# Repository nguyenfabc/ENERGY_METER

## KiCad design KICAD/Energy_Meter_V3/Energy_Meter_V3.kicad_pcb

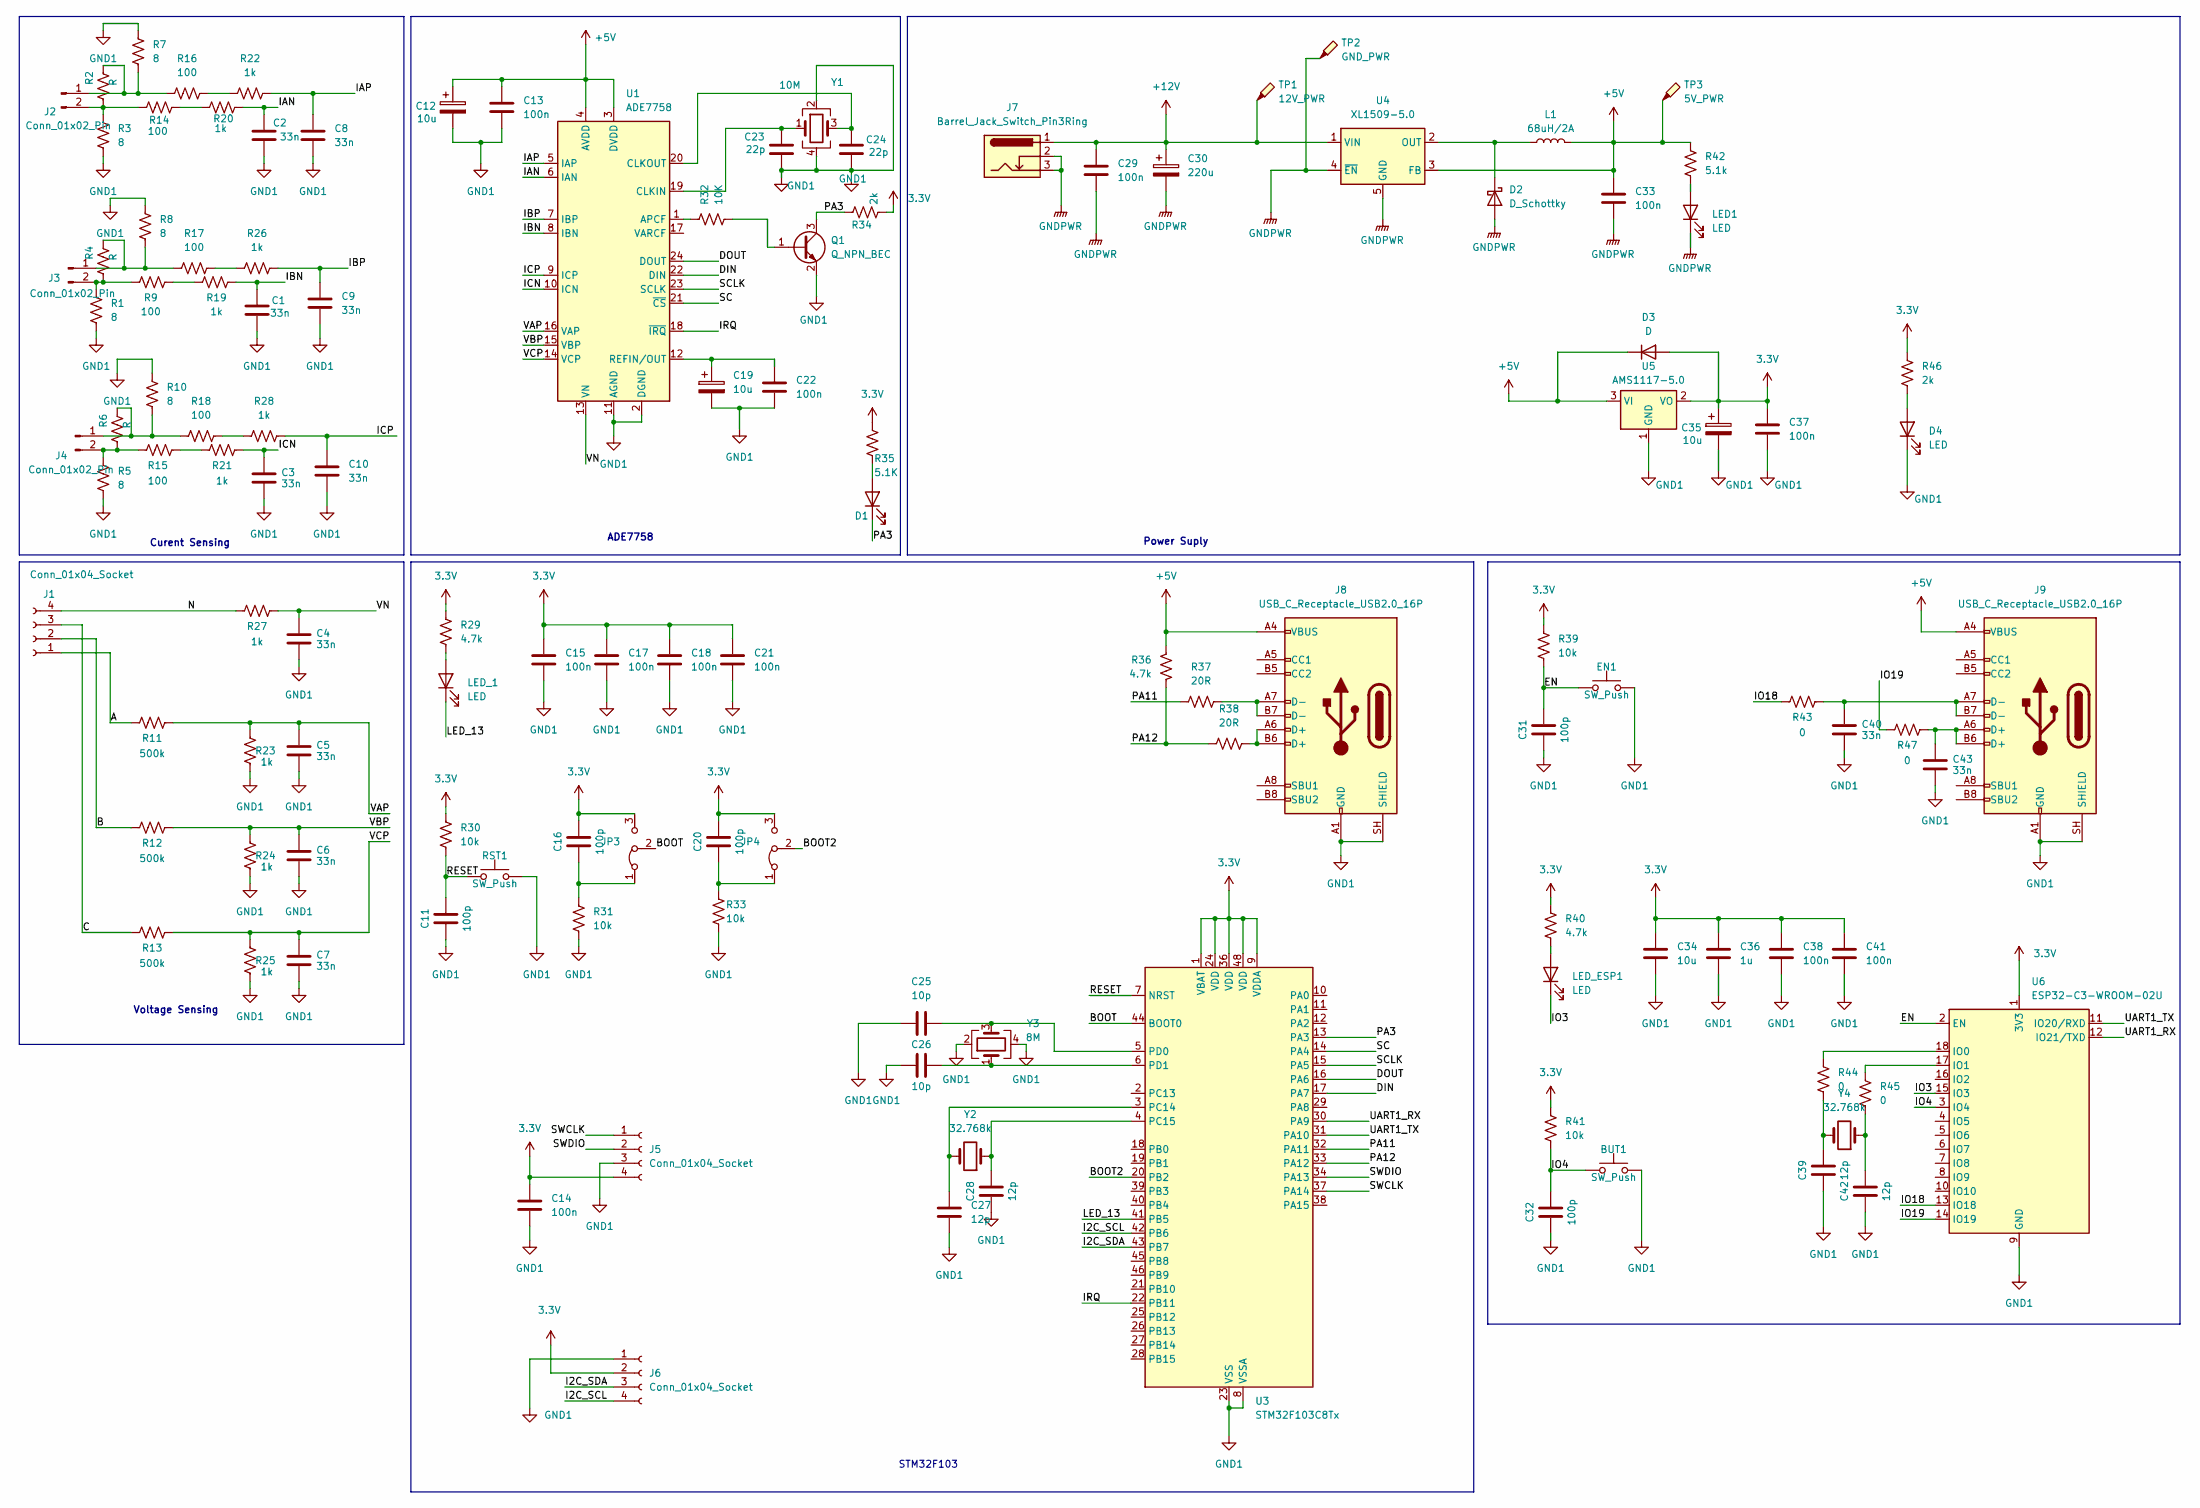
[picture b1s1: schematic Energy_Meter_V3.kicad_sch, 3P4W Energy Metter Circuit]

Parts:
BUT1: SW_Push; SW_SPST_CK_RS282G05A3
C1, C2, C3, C4, C5, C6, C7, C8, C9, C10, C40, C43: 33n; C_0603_1608Metric_Pad1.08x0.95mm_HandSolder
C11, C16, C20, C31, C32: 100p; C_0603_1608Metric_Pad1.08x0.95mm_HandSolder
C12, C19: 10u; CP_EIA-3216-10_Kemet-I_HandSolder
C13, C14, C15, C17, C18, C21, C22, C29, C33, C37, C38, C41: 100n; C_0603_1608Metric_Pad1.08x0.95mm_HandSolder
C23, C24: 22p; C_0603_1608Metric_Pad1.08x0.95mm_HandSolder
C25, C26: 10p; C_0603_1608Metric_Pad1.08x0.95mm_HandSolder
C27, C28, C39, C42: 12p; C_0603_1608Metric_Pad1.08x0.95mm_HandSolder
C30: 220u; CP_Elec_6.3x7.7
C34: 10u; C_0603_1608Metric_Pad1.08x0.95mm_HandSolder
C35: 10u; CP_Elec_4x5.4
C36: 1u; C_0603_1608Metric_Pad1.08x0.95mm_HandSolder
D1, D4: LED; LED_0805_2012Metric_Pad1.15x1.40mm_HandSolder
D2: D_Schottky; D_SMA_Handsoldering
D3: D; D_SMA_Handsoldering
EN1: SW_Push; SW_SPST_CK_RS282G05A3
J1: Conn_01x04_Socket; TerminalBlock_Phoenix_MKDS-1,5-4_1x04_P5.00mm_Horizontal
J2, J3, J4: Conn_01x02_Pin; TerminalBlock_Phoenix_MKDS-1,5-2_1x02_P5.00mm_Horizontal
J5: Conn_01x04_Socket; PinHeader_1x04_P2.54mm_Vertical
J6: Conn_01x04_Socket; PinSocket_1x04_P2.54mm_Vertical
J7: Barrel_Jack_Switch_Pin3Ring; BarrelJack_Kycon_KLDX-0202-xC_Horizontal
J8, J9: USB_C_Receptacle_USB2.0_16P; USB_C_Receptacle_Palconn_UTC16-G
JP3, JP4: Jumper_3_Bridged12; PinHeader_1x03_P2.54mm_Vertical
L1: 68uH/2A; L_Bourns_SRP7028A_7.3x6.6mm
LED1: LED; LED_0805_2012Metric_Pad1.15x1.40mm_HandSolder
LED_1: LED; LED_0805_2012Metric_Pad1.15x1.40mm_HandSolder
LED_ESP1: LED; LED_0805_2012Metric_Pad1.15x1.40mm_HandSolder
Q1: Q_NPN_BEC; SOT-23
R1, R3, R5, R7, R8, R10: 8; R_0603_1608Metric_Pad0.98x0.95mm_HandSolder
R2, R4, R6: R; R_0603_1608Metric_Pad0.98x0.95mm_HandSolder
R9, R14, R15, R16, R17, R18: 100; R_0603_1608Metric_Pad0.98x0.95mm_HandSolder
R11, R12, R13: 500k; R_0603_1608Metric_Pad0.98x0.95mm_HandSolder
R19, R20, R21, R22, R23, R24, R25, R26, R27, R28: 1k; R_0603_1608Metric_Pad0.98x0.95mm_HandSolder
R29, R36, R40: 4.7k; R_0603_1608Metric_Pad0.98x0.95mm_HandSolder
R30, R31, R33, R39, R41: 10k; R_0603_1608Metric_Pad0.98x0.95mm_HandSolder
R32: 10K; R_0603_1608Metric_Pad0.98x0.95mm_HandSolder
R34, R46: 2k; R_0603_1608Metric_Pad0.98x0.95mm_HandSolder
R35: 5.1K; R_0603_1608Metric_Pad0.98x0.95mm_HandSolder
R37, R38: 20R; R_0603_1608Metric_Pad0.98x0.95mm_HandSolder
R42: 5.1k; R_0603_1608Metric_Pad0.98x0.95mm_HandSolder
R43, R44, R45, R47: 0; R_0603_1608Metric_Pad0.98x0.95mm_HandSolder
RST1: SW_Push; SW_SPST_CK_RS282G05A3
TP1: 12V_PWR; TestPoint_Loop_D1.80mm_Drill1.0mm_Beaded
TP2: GND_PWR; TestPoint_Loop_D1.80mm_Drill1.0mm_Beaded
TP3: 5V_PWR; TestPoint_Loop_D1.80mm_Drill1.0mm_Beaded
U1: ADE7758; SOIC-24W_7.5x15.4mm_P1.27mm
U3: STM32F103C8Tx; LQFP-48_7x7mm_P0.5mm
U4: XL1509-5.0; SOIC-8_3.9x4.9mm_P1.27mm
U5: AMS1117-5.0; SOT-223-3_TabPin2
U6: ESP32-C3-WROOM-02U
Y1: 10M; Crystal_SMD_5032-4Pin_5.0x3.2mm
Y2, Y4: 32.768k; Crystal_SMD_3215-2Pin_3.2x1.5mm
Y3: 8M; Crystal_SMD_5032-4Pin_5.0x3.2mm

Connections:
3.3V: C14.2, C15.2, C16.2, C17.2, C18.2, C20.2, C21.2, C34.2, C35.1, C36.2, C37.1, C38.2, C41.2, D3.2 (A), J5.4, J6.2, JP3.3 (B), JP4.3 (B), R29.1, R30.1, R34.1, R35.2, R39.1, R40.1, R41.1, R46.2, U3.1 (VBAT), U3.9 (VDDA), U3.24 (VDD), U3.36 (VDD), U3.48 (VDD), U5.2 (VO), U6.1 (3V3)
+5V: C12.1, C13.1, C33.2, D3.1 (K), J8.A4 (VBUS), J8.A9 (VBUS), J8.B4 (VBUS), J8.B9 (VBUS), J9.A4 (VBUS), J9.A9 (VBUS), J9.B4 (VBUS), J9.B9 (VBUS), L1.2, R36.1, R42.1, TP3.1 (1_1), U1.3 (DVDD), U1.4 (AVDD), U4.3 (FB), U5.3 (VI)
+12V: C29.2, C30.1, J7.1, TP1.1 (1_1), U4.1 (VIN)
/A: J1.1, R11.1
/B: J1.2, R12.1
/BOOT: JP3.2 (C), U3.44 (BOOT0)
/BOOT2: JP4.2 (C), U3.20 (PB2)
/C: J1.3, R13.1
/DIN: U1.22 (DIN), U3.17 (PA7)
/DOUT: U1.24 (DOUT), U3.16 (PA6)
/EN: C31.2, EN1.1, R39.2, U6.2 (EN)
/I2C_SCL: J6.4, U3.42 (PB6)
/I2C_SDA: J6.3, U3.43 (PB7)
/IAN: C2.1, R20.2, U1.6 (IAN)
/IAP: C8.1, R22.2, U1.5 (IAP)
/IBN: C1.1, R19.2, U1.8 (IBN)
/IBP: C9.1, R26.2, U1.7 (IBP)
/ICN: C3.1, R21.2, U1.10 (ICN)
/ICP: C10.1, R28.2, U1.9 (ICP)
/IO3: LED_ESP1.1 (K), U6.15 (IO3)
/IO4: BUT1.1, C32.2, R41.2, U6.3 (IO4)
/IO18: R43.1, U6.13 (IO18)
/IO19: R47.1, U6.14 (IO19)
/IRQ: U1.18 (~IRQ), U3.22 (PB11)
/LED_13: LED_1.1 (K), U3.41 (PB5)
/N: J1.4, R27.1
/PA3: D1.1 (K), Q1.3 (C), R34.2, U3.13 (PA3)
/PA11: R37.1, U3.32 (PA11)
/PA12: R36.2, R38.1, U3.33 (PA12)
/RESET: C11.2, R30.2, RST1.1, U3.7 (NRST)
/SC: U1.21 (~CS), U3.14 (PA4)
/SCLK: U1.23 (SCLK), U3.15 (PA5)
/SWCLK: J5.1, U3.37 (PA14)
/SWDIO: J5.2, U3.34 (PA13)
/UART1_RX: U3.30 (PA9), U6.12 (IO21/TXD)
/UART1_TX: U3.31 (PA10), U6.11 (IO20/RXD)
/VAP: C5.1, R11.2, R23.2, U1.16 (VAP)
/VBP: C6.1, R12.2, R24.2, U1.15 (VBP)
/VCP: C7.1, R13.2, R25.2, U1.14 (VCP)
/VN: C4.1, R27.2, U1.13 (VN)
GND1: BUT1.2, C1.2, C2.2, C3.2, C4.2, C5.2, C6.2, C7.2, C8.2, C9.2, C10.2, C11.1, C12.2, C13.2, C14.1, C15.1, C17.1, C18.1, C19.2, C21.1, C22.2, C23.2, C24.2, C25.1, C26.1, C27.1, C28.1, C31.1, C32.1, C34.1, C35.2, C36.1, C37.2, C38.1, C39.1, C40.2, C41.1, C42.1, C43.2, D4.1 (K), EN1.2, J5.3, J6.1, J8.A1 (GND), J8.A12 (GND), J8.B1 (GND), J8.B12 (GND), J8.SH (SHIELD), J9.A1 (GND), J9.A12 (GND), J9.B1 (GND), J9.B12 (GND), J9.SH (SHIELD), Q1.2 (E), R1.2, R3.2, R5.2, R7.1, R8.1, R10.1, R23.1, R24.1, R25.1, R31.2, R33.2, RST1.2, U1.2 (DGND), U1.11 (AGND), U3.8 (VSSA), U3.23 (VSS), U3.35 (VSS), U3.47 (VSS), U5.1 (GND), U6.9 (GND), U6.19 (GND), Y1.2, Y1.4, Y3.2, Y3.4
GNDPWR: C29.1, C30.2, C33.1, D2.2 (A), J7.2, J7.3, LED1.1 (K), TP2.1 (1_1), U4.4 (~EN), U4.5 (GND), U4.6 (GND), U4.7 (GND), U4.8 (GND)
unnamed: C39.2, R44.2, Y4.2
unnamed: C40.1, J9.A7 (D-), J9.B7 (D-), R43.2
unnamed: C42.2, R45.2, Y4.1
unnamed: C43.1, J9.A6 (D+), J9.B6 (D+), R47.2
unnamed: D1.2 (A), R35.1
unnamed: D2.1 (K), L1.1, U4.2 (OUT)
unnamed: D4.2 (A), R46.1
unnamed: J2.1, R2.2, R7.2, R16.1
unnamed: J2.2, R2.1, R3.1, R14.1
unnamed: J3.1, R4.2, R8.2, R17.1
unnamed: J3.2, R1.1, R4.1, R9.1
unnamed: J4.1, R6.2, R10.2, R18.1
unnamed: J4.2, R5.1, R6.1, R15.1
unnamed: J8.A6 (D+), J8.B6 (D+), R38.2
unnamed: J8.A7 (D-), J8.B7 (D-), R37.2
unnamed: C16.1, JP3.1 (A), R31.1
unnamed: C20.1, JP4.1 (A), R33.1
unnamed: LED1.2 (A), R42.2
unnamed: LED_1.2 (A), R29.2
unnamed: LED_ESP1.2 (A), R40.2
unnamed: Q1.1 (B), R32.1
unnamed: R14.2, R20.1
unnamed: R15.2, R21.1
unnamed: R16.2, R22.1
unnamed: R17.2, R26.1
unnamed: R18.2, R28.1
unnamed: R9.2, R19.1
unnamed: R32.2, U1.1 (APCF)
unnamed: C23.1, U1.19 (CLKIN), Y1.1
unnamed: C24.1, U1.20 (CLKOUT), Y1.3
unnamed: C19.1, C22.1, U1.12 (REFIN/OUT)
unnamed: C27.2, U3.3 (PC14), Y2.2
unnamed: C28.2, U3.4 (PC15), Y2.1
unnamed: C25.2, U3.5 (PD0), Y3.3
unnamed: C26.2, U3.6 (PD1), Y3.1
unnamed: R44.1, U6.18 (IO0)
unnamed: R45.1, U6.17 (IO1)

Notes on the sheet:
Power Suply
Voltage Sensing
STM32F103
Curent Sensing
ADE7758

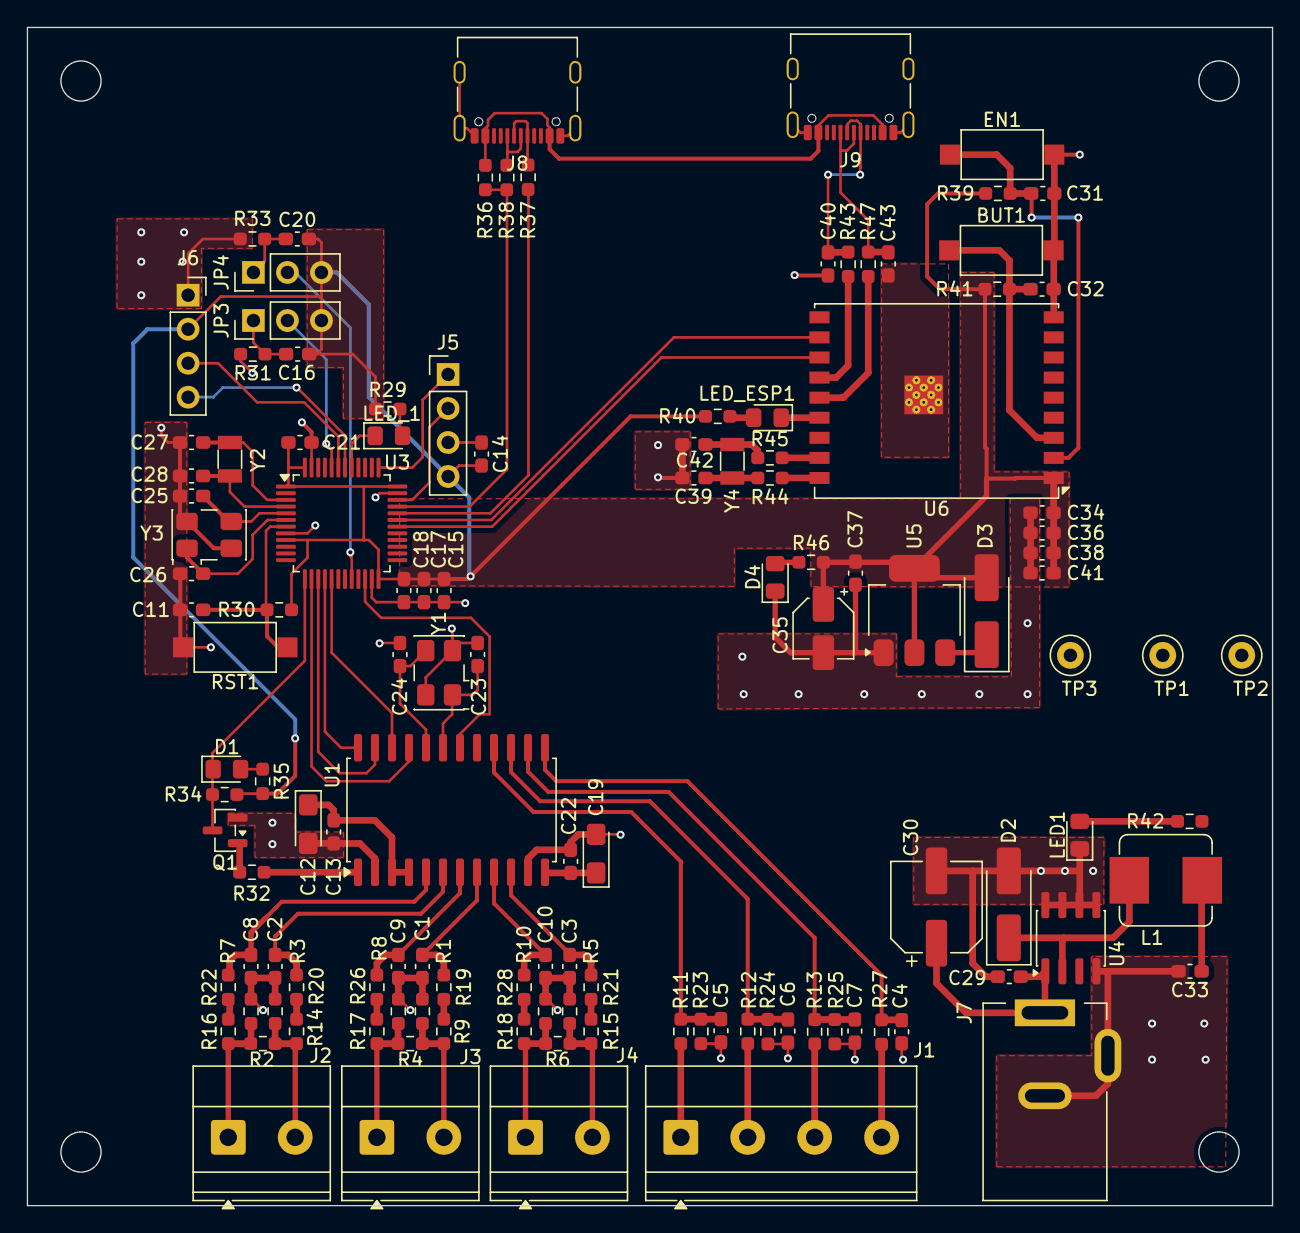
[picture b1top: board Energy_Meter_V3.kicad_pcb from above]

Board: 2 copper layers, 93.0 x 88.0 mm, 125 parts (0 on the bottom side), 79 nets.

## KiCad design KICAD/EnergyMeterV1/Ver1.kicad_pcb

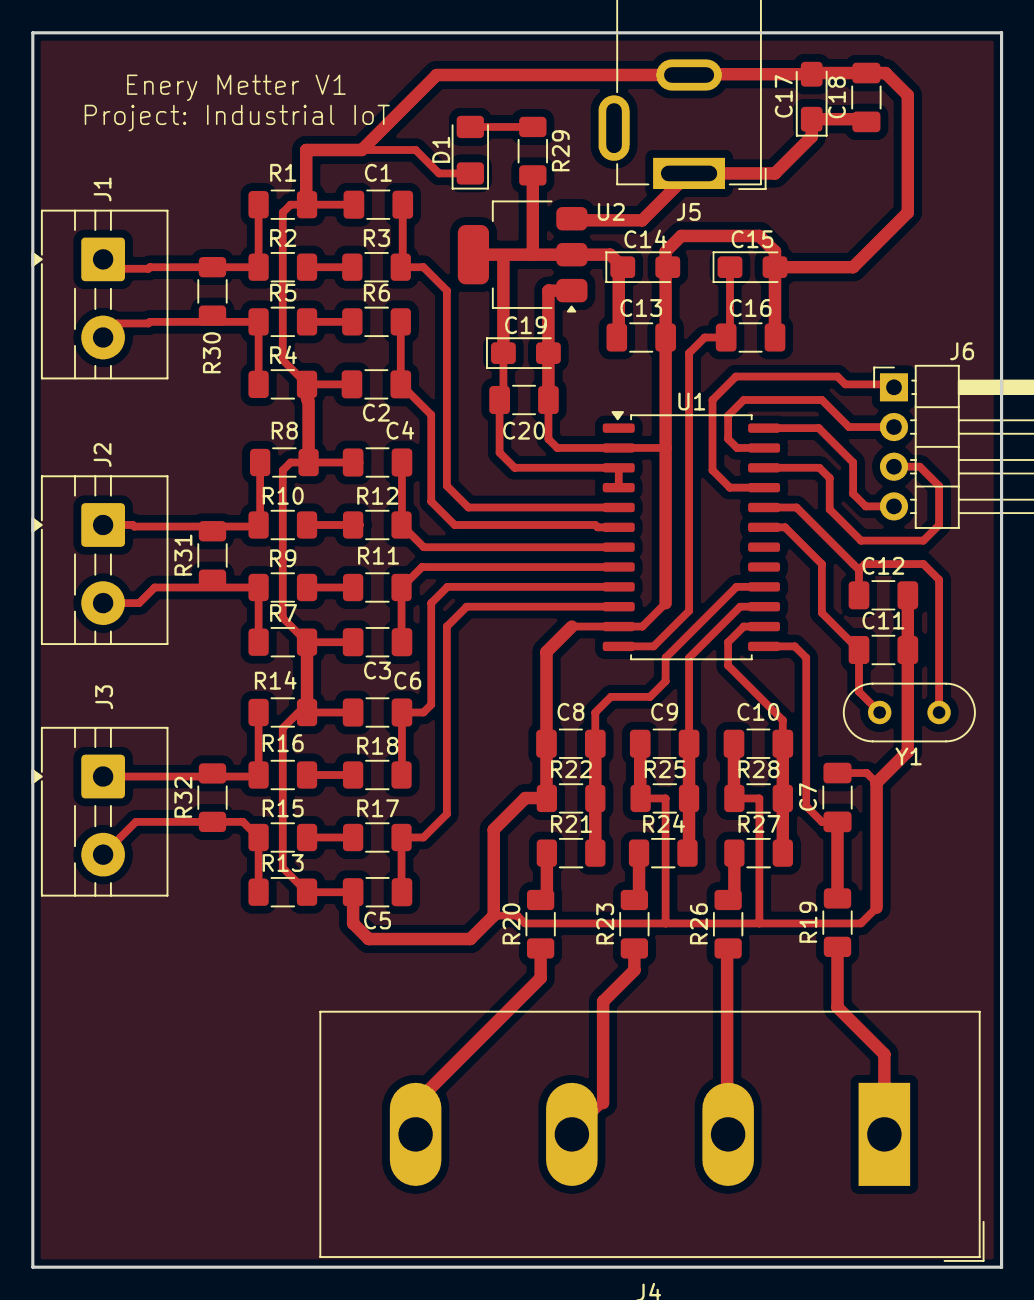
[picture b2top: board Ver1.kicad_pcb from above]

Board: 2 copper layers, 62.0 x 79.0 mm, 62 parts (0 on the bottom side), 40 nets.

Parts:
C1, C2, C3, C4, C5, C6, C7, C8, C9, C10: 33n; C_1206_3216Metric_Pad1.33x1.80mm_HandSolder
C11, C12: 22p; C_1206_3216Metric_Pad1.33x1.80mm_HandSolder
C13, C16, C18, C20: 100n; C_1206_3216Metric_Pad1.33x1.80mm_HandSolder
C14, C15, C17, C19: 10u; CP_EIA-3216-10_Kemet-I_HandSolder
D1: LED; LED_1206_3216Metric_Pad1.42x1.75mm_HandSolder
J1, J2, J3: Conn_01x02_Pin; TerminalBlock_MaiXu_MX126-5.0-02P_1x02_P5.00mm
J4: Conn_01x04_Socket; TerminalBlock_Dinkle_DT-55-B01X-04_P10.00mm
J5: Jack-DC; BarrelJack_GCT_DCJ200-10-A_Horizontal
J6: Conn_01x04_Socket; PinHeader_1x04_P2.54mm_Horizontal
R1, R4, R7, R8, R13, R14: 8; R_1206_3216Metric_Pad1.30x1.75mm_HandSolder
R2, R5, R9, R10, R15, R16: 100; R_1206_3216Metric_Pad1.30x1.75mm_HandSolder
R3, R6, R11, R12, R17, R18, R19, R22, R25, R28: 1k; R_1206_3216Metric_Pad1.30x1.75mm_HandSolder
R20, R21, R23, R24, R26, R27: 500k; R_1206_3216Metric_Pad1.30x1.75mm_HandSolder
R29: 2k; R_1206_3216Metric_Pad1.30x1.75mm_HandSolder
R30, R31, R32: R; R_1206_3216Metric_Pad1.30x1.75mm_HandSolder
U1: ADE7758; SOIC-24W_7.5x15.4mm_P1.27mm
U2: AMS1117-5.0; SOT-223-3_TabPin2
Y1: 10MHz; Crystal_HC52-8mm_Vertical

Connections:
/IAN: C2.1, R6.2, U1.6 (IAN)
/IAP: C1.1, R3.2, U1.5 (IAP)
/IBN: C3.1, R11.2, U1.8 (IBN)
/IBP: C4.1, R12.2, U1.7 (IBP)
/ICN: C5.1, R17.2, U1.10 (ICN)
/ICP: C6.1, R18.2, U1.9 (ICP)
/VAP: C8.1, R21.2, R22.2, U1.16 (VAP)
/VBP: C9.1, R24.2, R25.2, U1.15 (VBP)
/VCP: C10.1, R27.2, R28.2, U1.14 (VCP)
/VN: C7.1, R19.2, U1.13 (VN)
/Va: J4.4, R20.1
/Vn: J4.1, R19.1
GND1: C1.2, C2.2, C3.2, C4.2, C5.2, C6.2, C7.2, C8.2, C9.2, C10.2, C11.2, C12.2, C13.2, C14.2, C15.2, C16.2, C17.2, C18.2, C19.2, C20.2, D1.1 (K), J5.2, R1.1, R4.2, R7.2, R8.1, R13.2, R14.1, R22.1, R25.1, R28.1, U1.2 (DGND), U1.11 (AGND), U2.1 (GND)
unnamed: D1.2 (A), R29.1
unnamed: J1.1, R1.2, R2.1, R30.2
unnamed: J1.2, R4.1, R5.1, R30.1
unnamed: J2.1, R8.2, R10.1, R31.2
unnamed: J2.2, R7.1, R9.1, R31.1
unnamed: J3.1, R14.2, R16.1, R32.2
unnamed: J3.2, R13.1, R15.1, R32.1
unnamed: J4.2, R26.1
unnamed: J4.3, R23.1
unnamed: J6.1, U1.21 (~CS)
unnamed: J6.2, U1.23 (SCLK)
unnamed: J6.3, U1.22 (DIN)
unnamed: J6.4, U1.24 (DOUT)
unnamed: R2.2, R3.1
unnamed: R5.2, R6.1
unnamed: R10.2, R12.1
unnamed: R9.2, R11.1
unnamed: R15.2, R17.1
unnamed: R16.2, R18.1
unnamed: R20.2, R21.1
unnamed: R23.2, R24.1
unnamed: R26.2, R27.1
unnamed: C11.1, U1.19 (CLKIN), Y1.2
unnamed: C12.1, U1.20 (CLKOUT), Y1.1
unnamed: C15.1, C16.1, U1.12 (REFIN/OUT)
unnamed: C17.1, C18.1, J5.1, U2.3 (VI)
VDD: C13.1, C14.1, C19.1, C20.1, R29.2, U1.3 (DVDD), U1.4 (AVDD), U2.2 (VO)

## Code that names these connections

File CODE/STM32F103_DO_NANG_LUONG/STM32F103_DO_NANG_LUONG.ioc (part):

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Mcu.Name=STM32F103C(8-B)Tx
Mcu.Package=LQFP48
Mcu.UserName=STM32F103C8Tx
PA10.Mode=Asynchronous
PA10.Signal=USART1_RX
PA13.Mode=Serial_Wire
PA13.Signal=SYS_JTMS-SWDIO
PA14.Mode=Serial_Wire
PA14.Signal=SYS_JTCK-SWCLK
PA3.Signal=GPIO_Input
PA5.Mode=Full_Duplex_Master
PA5.Signal=SPI1_SCK
PA6.Mode=Full_Duplex_Master
PA6.Signal=SPI1_MISO
PA7.Mode=Full_Duplex_Master
PA7.Signal=SPI1_MOSI
PA9.Mode=Asynchronous
PA9.Signal=USART1_TX
PB11.Signal=GPIO_Input
PB6.Mode=I2C
PB6.Signal=I2C1_SCL
PB7.Mode=I2C
PB7.Signal=I2C1_SDA
PD0-OSC_IN.Mode=HSE-External-Oscillator
PD0-OSC_IN.Signal=RCC_OSC_IN
PD1-OSC_OUT.Mode=HSE-External-Oscillator
PD1-OSC_OUT.Signal=RCC_OSC_OUT
board=custom

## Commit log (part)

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2026-04-28 Lan dau tai len
